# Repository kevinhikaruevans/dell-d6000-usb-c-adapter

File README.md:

# dell-d6000-usb-c-adapter
KiCAD project to replace the proprietary USB-C cable.

The schematic is seemingly correct: it's been tested at low-speeds and it correctly negotiates USB, things like audio, HDMI, (slow) ethernet work. However I can't seem to get the required differential impedances correct using a flex PCB with [approximate parameters](https://jlcpcb.com/capabilities/flex-pcb-capabilities):

- Core $\varepsilon_r = 3.3$, Coverlay $\varepsilon_r = 2.9$, core polyimide thickness: 25 um
- FPC finished thickness: 0.2 mm +/- 0.05mm (?)
- Copper thickness: 35 um (1 oz)

KiCAD's calculator doesn't like these values and doing it by hand leads to strange calculations. I also tried to simulate it using openEMS but to no avail. So while the PCB might work at low speeds, it will likely not work at high (near GbE) speeds... at least until somebody redoes this project.

## Original

Here's the original pin out:

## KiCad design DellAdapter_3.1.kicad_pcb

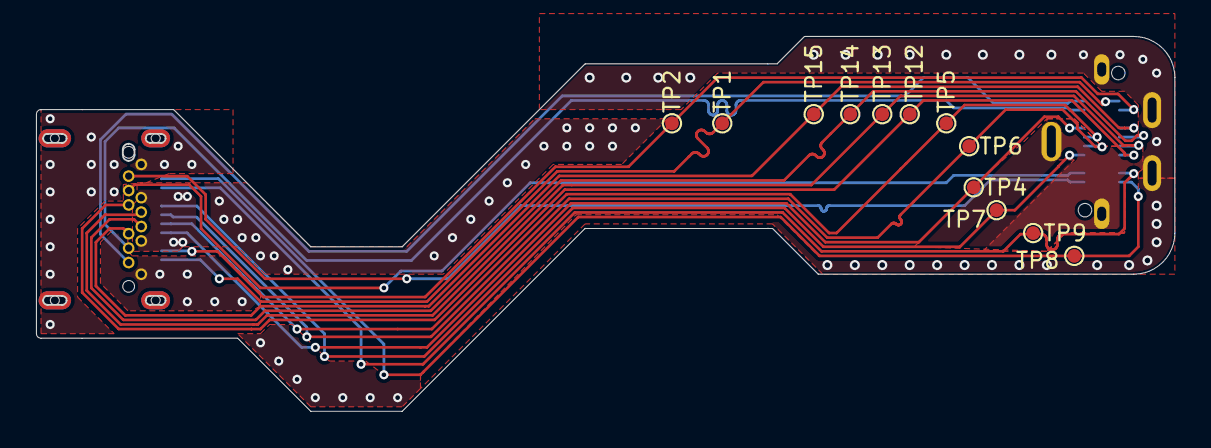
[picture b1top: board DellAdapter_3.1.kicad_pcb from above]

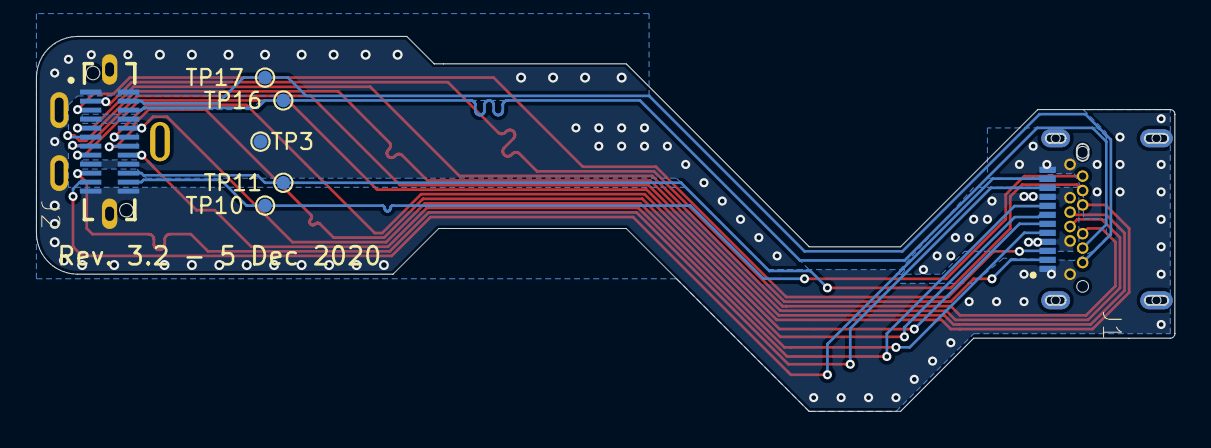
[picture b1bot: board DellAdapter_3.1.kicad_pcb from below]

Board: 2 copper layers, 63.2 x 20.8 mm, 19 parts (7 on the bottom side), 18 nets.

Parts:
J1: USB4065-XX-X_REVA; GCT_USB4065-XX-X_REVA
J2: USB4151-GF-C_REVA; GCT_USB4151-GF-C_REVA
TP1, TP2, TP3, TP4, TP5, TP6, TP7, TP8, TP9, TP10, TP11, TP12, TP13, TP14, TP15, TP16, TP17: TestPoint; TestPoint_Pad_D0.75mm

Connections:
/CC1: J1.A5, J2.B8, TP4.1
/CC2: J1.B5, J2.A8, TP12.1
/D1+: J1.A6, J2.B7, TP5.1
/D1-: J1.A7, J2.B6, TP6.1
/D2+: J1.B6, J2.A7, TP13.1
/D2-: J1.B7, J2.A6, TP14.1
/GND: J1.1, J1.2, J1.3, J1.4, J1.A1, J1.A12, J1.B1, J1.B12, J2.A1, J2.A12, J2.B1, J2.B12, J2.S1, J2.S2, J2.S3, J2.S4, J2.S5
/RX1+: J1.B11, J2.B11, TP17.1
/RX1-: J1.B10, J2.B10, TP16.1
/RX2+: J1.A11, J2.A11, TP8.1
/RX2-: J1.A10, J2.A10, TP9.1
/SBU1: J1.A8, J2.B5, TP7.1
/SBU2: J1.B8, J2.A5, TP15.1
/TX1+: J1.A2, J2.A2, TP1.1
/TX1-: J1.A3, J2.A3, TP2.1
/TX2+: J1.B2, J2.B2, TP10.1
/TX2-: J1.B3, J2.B3, TP11.1
/VBUS: J1.A4, J1.A9, J1.B4, J1.B9, J2.A4, J2.A9, J2.B4, J2.B9, TP3.1

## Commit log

2020-12-04 rm unused instructions
2020-12-13 increase pad size; panelize
2021-01-14 shrink tolerances on footprints
